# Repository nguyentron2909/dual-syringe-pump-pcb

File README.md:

# Dual Syringe Pump Controller (ESP32 + TMC2209)

This repository contains the KiCad hardware design for a compact, battery-powered dual stepper motor controller. Designed around the **ESP32-WROOM-32** for wireless control and **TMC2209** silent stepper drivers, this board is optimized for high-precision multi-channel micropump systems and drug delivery applications.

## 🛠 Hardware Architecture

The project is divided into three main functional blocks:

### 1. Power Management & Charging
A robust power subsystem designed to handle both wall power and battery operation, ensuring uninterrupted dispensing.
* **Charging:** Integrated **TP5100** battery charger for 2S Li-ion setups.
* **Regulation:** * **Buck Converter (LM2596):** Stepping down input voltage to 5V for logic.
    * **LDO (AMS1117-3.3):** Providing stable 3.3V for the ESP32 and sensors.
    * **Dual Boost Converters (XL6009):** Independent 12V rails (`+12V_1` and `+12V_2`) to power the stepper drivers, allowing for high-torque performance even on battery power.

### 2. Main Control & Interface
The logic center of the board, featuring:
* **MCU:** ESP32-WROOM-32 with USB-C programming via **CH340C** and an auto-reset circuit.
* **Position Feedback:** Support for dual **AS5600** magnetic encoders via I2C for closed-loop monitoring and exact position tracking.
* **User Interface:** Headers for an external screen, status LEDs, and additional tactile buttons.

### 3. Stepper Driver Stage
High-performance motor control featuring:
* **Drivers:** Dual **TMC2209-LA** drivers (U6 & U7).
* **Communication:** UART interface mapped to the ESP32 for advanced configuration (StealthChop, StallGuard, dynamic current limits).
* **Optimization:** Support for hardware-level current sensing. *(Note: RS resistors should be desoldered from the current sensing module for better performance, as noted in the schematic).*

---

## 📋 Key Specifications

| Component | Specification |
| :--- | :--- |
| **Microcontroller** | ESP32-WROOM-32 (Wi-Fi/BT) |
| **Stepper Drivers** | 2x TMC2209 (SilentStepStick style) |
| **Input Voltage** | +12V Adapter or 2S Li-ion Battery |
| **Logic Voltage** | 3.3V and 5V |
| **Sensors** | 2x AS5600 Magnetic Encoders |
| **USB Interface** | USB-C (CH340C) |

---

## 📂 PCB layout

---

## 📝 Design Notes

* **Current Sensing:** Ensure you desolder the RS resistors from the driver modules if you are using an external current sensing setup to avoid interference.
* **Thermal Management:** Provide adequate cooling (heatsinks/airflow) for the XL6009 boost converters and TMC2209 drivers if running the stepper motors at high continuous currents.
* **Big thanks to google gemini for writting this for me :D

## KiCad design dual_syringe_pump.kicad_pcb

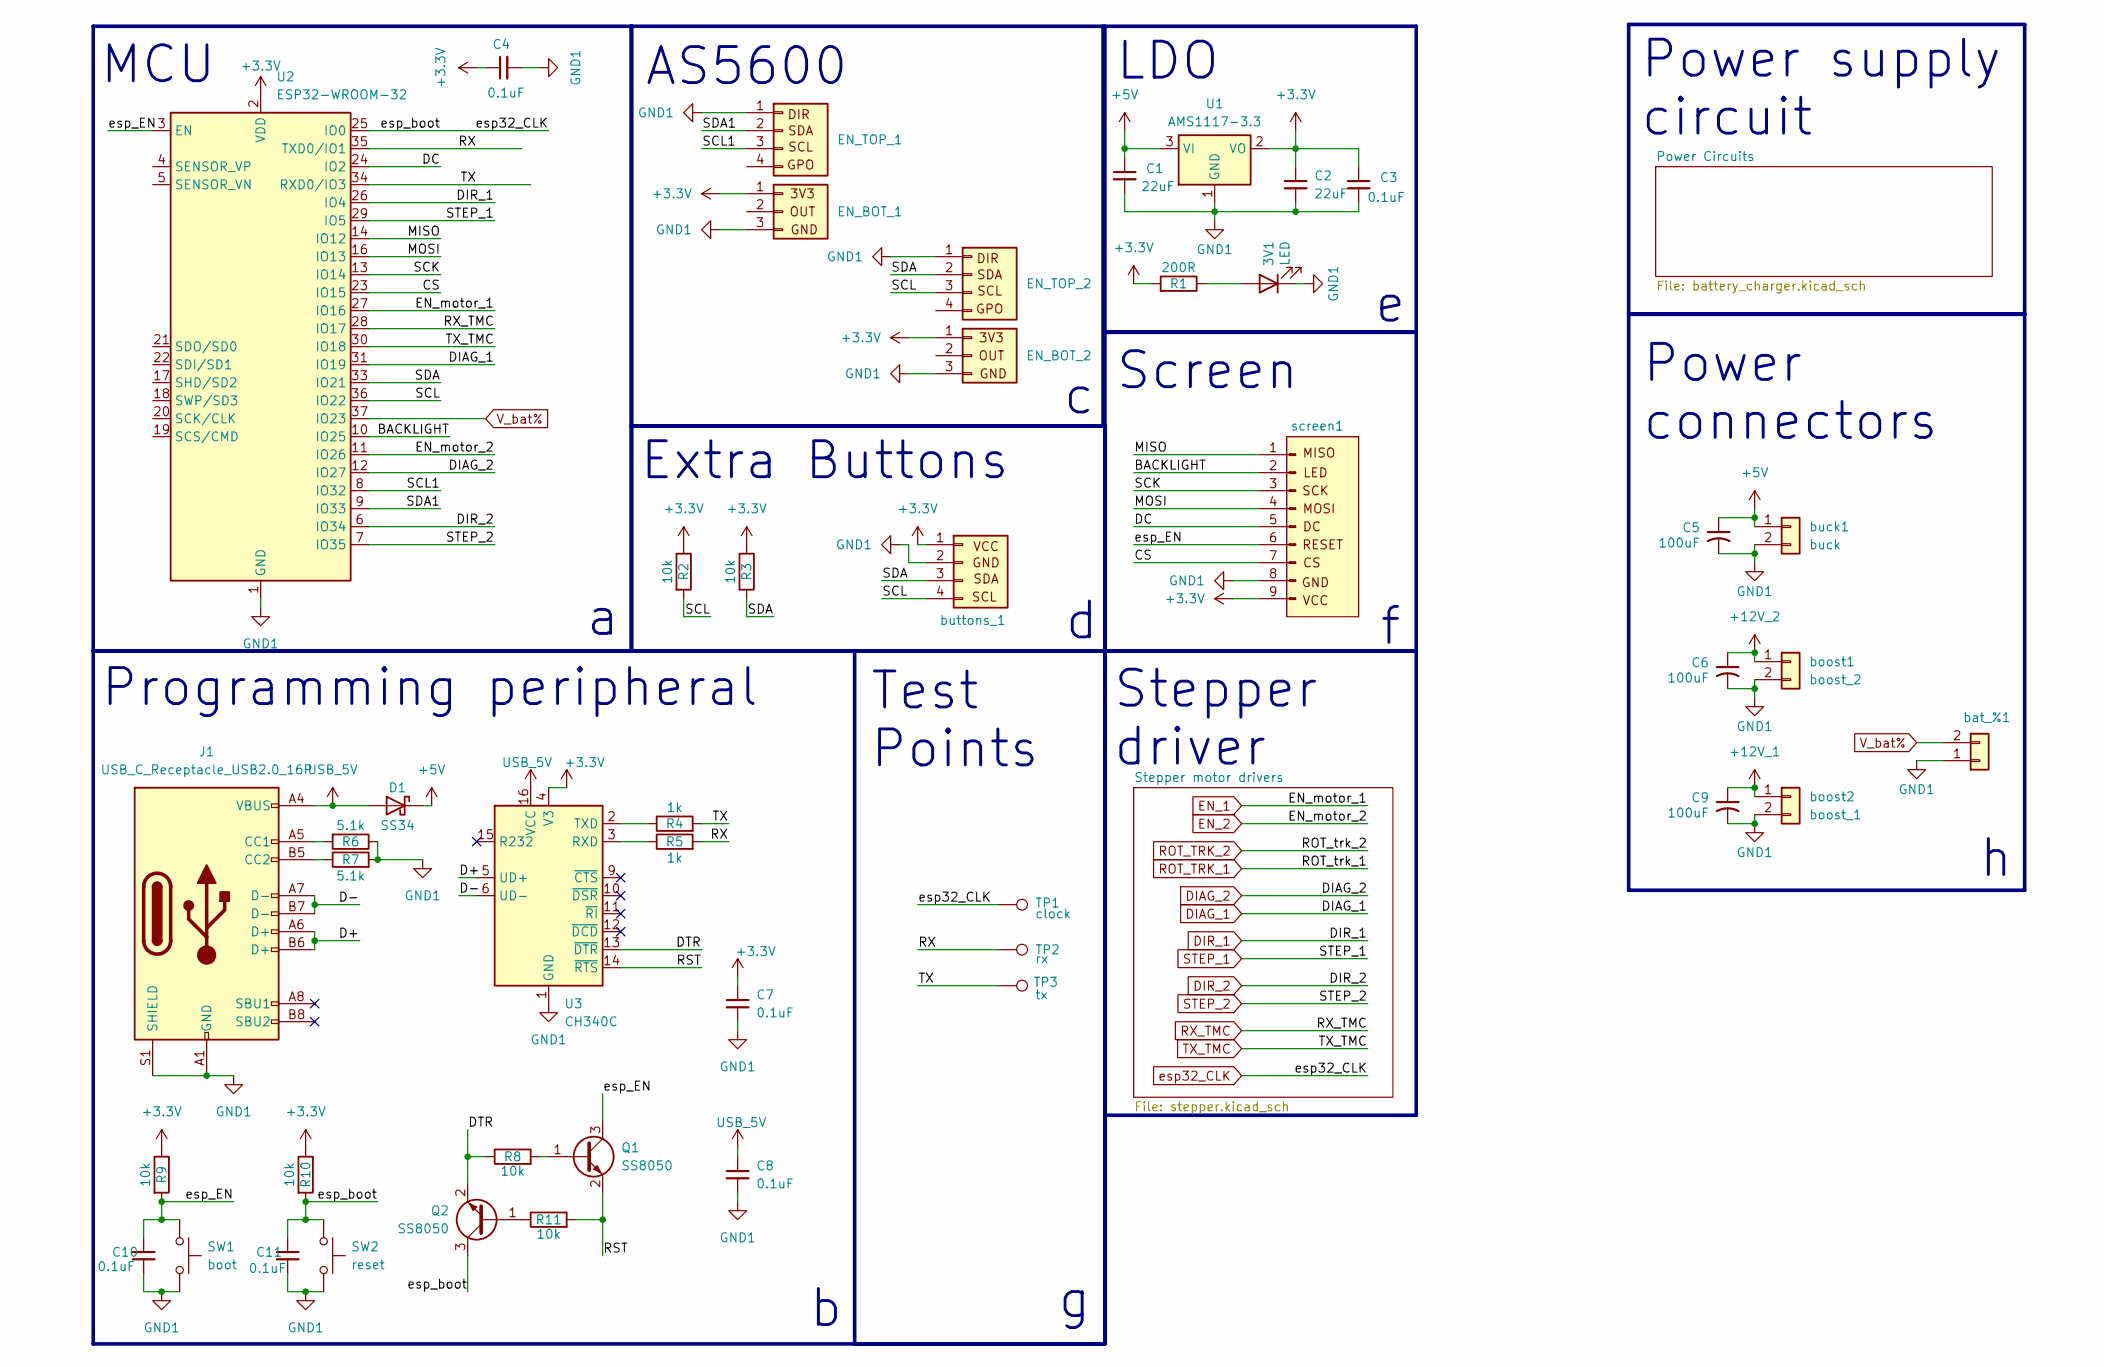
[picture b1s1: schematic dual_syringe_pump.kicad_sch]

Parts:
3V1: LED; LED_0603_1608Metric_Pad1.05x0.95mm
C1, C2: 22uF; C_0603
C3, C4, C7, C8, C10, C11: 0.1uF; C_0603
C5, C6, C9: 100uF; C_Elec_6.3x7.7
D1: SS34; D_SMA
EN_BOT_1, EN_BOT_2: Conn_01x03; PinHeader_1x03_P2.54mm_Vertical
EN_TOP_1, EN_TOP_2: Conn_01x04; PinHeader_1x04_P2.54mm_Vertical; Part Number 1-0401FBV0T
J1: USB_C_Receptacle_USB2.0_16P; USB_C_Receptacle_GCT_USB4105-xx-A_16P_TopMnt_Horizontal
Q1, Q2: SS8050; SOT-23
R1: 200R; R_0603
R2, R3, R8, R9, R10, R11: 10k; R_0603
R4, R5: 1k; R_0603
R6, R7: 5.1k; R_0603
SW1: boot; SW_SPST_CK_RS282G05A3
SW2: reset; SW_SPST_CK_RS282G05A3
TP1: clock; TestPoint_Pad_D1.0mm
TP2: rx; TestPoint_Pad_D1.0mm
TP3: tx; TestPoint_Pad_D1.0mm
U1: AMS1117-3.3; SOT-223-3_TabPin2
U2: ESP32-WROOM-32
U3: CH340C; SOIC-16_3.9x9.9mm_P1.27mm
bat_%1: battery _percentage; PinHeader_1x02_P2.54mm_Vertical; Part Number 1-0201FBV0T
boost1: boost_2; JST_VH_B2P-VH-B_1x02_P3.96mm_Vertical; Part Number 1-0201FBV0T
boost2: boost_1; JST_VH_B2P-VH-B_1x02_P3.96mm_Vertical; Part Number 1-0201FBV0T
buck1: buck; JST_VH_B2P-VH-B_1x02_P3.96mm_Vertical; Part Number 1-0201FBV0T
buttons_1: Conn_01x04; PinHeader_1x04_P2.54mm_Vertical; Part Number 1-0401FBV0T
screen1: Conn_01x09_Pin; PinSocket_1x09_P2.54mm_Vertical

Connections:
+3.3V: C2.1, C3.1, C4.1, C7.1, EN_BOT_1.1, EN_BOT_2.1, R1.2, R2.1, R3.1, R9.1, R10.1, U1.2 (VO), U2.2 (VDD), U3.4 (V3), buttons_1.1, screen1.9; also elsewhere on the board
+5V: C1.1, C5.1, D1.1 (K), U1.3 (VI), buck1.1; also elsewhere on the board
+12V_1: C9.1, boost2.1; also elsewhere on the board
+12V_2: C6.1, boost1.1; also elsewhere on the board
/BACKLIGHT: U2.10 (IO25), screen1.2
/CS: U2.23 (IO15), screen1.7
/D+: J1.A6 (D+), J1.B6 (D+), U3.5 (UD+)
/D-: J1.A7 (D-), J1.B7 (D-), U3.6 (UD-)
/DC: U2.24 (IO2), screen1.5
/DTR: Q2.2 (E), R8.1, U3.13 (~DTR)
/MISO: U2.14 (IO12), screen1.1
/MOSI: U2.16 (IO13), screen1.4
/RST: Q1.2 (E), R11.2, U3.14 (~RTS)
/RX: R5.2, TP2.1 (1_1), U2.35 (TXD0/IO1)
/SCK: U2.13 (IO14), screen1.3
/SCL: EN_TOP_2.3, R2.2, U2.36 (IO22), buttons_1.4
/SCL1: EN_TOP_1.3, U2.8 (IO32)
/SDA: EN_TOP_2.2, R3.2, U2.33 (IO21), buttons_1.3
/SDA1: EN_TOP_1.2, U2.9 (IO33)
/TX: R4.2, TP3.1 (1_1), U2.34 (RXD0/IO3)
/esp_EN: C10.1, Q1.3 (C), R9.2, SW1.1, U2.3 (EN), screen1.6
DIAG_1: U2.31 (IO19); also elsewhere on the board
DIAG_2: U2.12 (IO27); also elsewhere on the board
DIR_1: U2.26 (IO4); also elsewhere on the board
DIR_2: U2.6 (IO34); also elsewhere on the board
EN_1: U2.27 (IO16); also elsewhere on the board
EN_2: U2.11 (IO26); also elsewhere on the board
GND1: 3V1.1 (K), C1.2, C2.2, C3.2, C4.2, C5.2, C6.2, C7.2, C8.2, C9.2, C10.2, C11.2, EN_BOT_1.3, EN_BOT_2.3, EN_TOP_1.1, EN_TOP_2.1, J1.A1 (GND), J1.A12 (GND), J1.B1 (GND), J1.B12 (GND), J1.S1 (SHIELD), R6.1, R7.2, SW1.2, SW2.2, U1.1 (GND), U2.1 (GND), U2.15 (GND), U2.38 (GND), U2.39 (GND), U3.1 (GND), bat_%1.1, boost1.2, boost2.2, buck1.2, buttons_1.2, screen1.8; also elsewhere on the board
unnamed: 3V1.2 (A), R1.1
unnamed: J1.A5 (CC1), R6.2
unnamed: J1.B5 (CC2), R7.1
unnamed: Q1.1 (B), R8.2
unnamed: Q2.1 (B), R11.1
unnamed: R5.1, U3.3 (RXD)
unnamed: R4.1, U3.2 (TXD)
RX_TMC: U2.28 (IO17); also elsewhere on the board
STEP_1: U2.29 (IO5); also elsewhere on the board
STEP_2: U2.7 (IO35); also elsewhere on the board
TX_TMC: U2.30 (IO18); also elsewhere on the board
USB_5V: C8.1, D1.2 (A), J1.A4 (VBUS), J1.A9 (VBUS), J1.B4 (VBUS), J1.B9 (VBUS), U3.16 (VCC)
V_bat%: U2.37 (IO23), bat_%1.2; also elsewhere on the board
esp32_CLK: C11.1, Q2.3 (C), R10.2, SW2.1, TP1.1 (1_1), U2.25 (IO0); also elsewhere on the board

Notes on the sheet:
Test Points
Power supply circuit
Screen
Programming peripheral
Extra Buttons
LDO
MCU
Stepper driver
AS5600
Power connectors

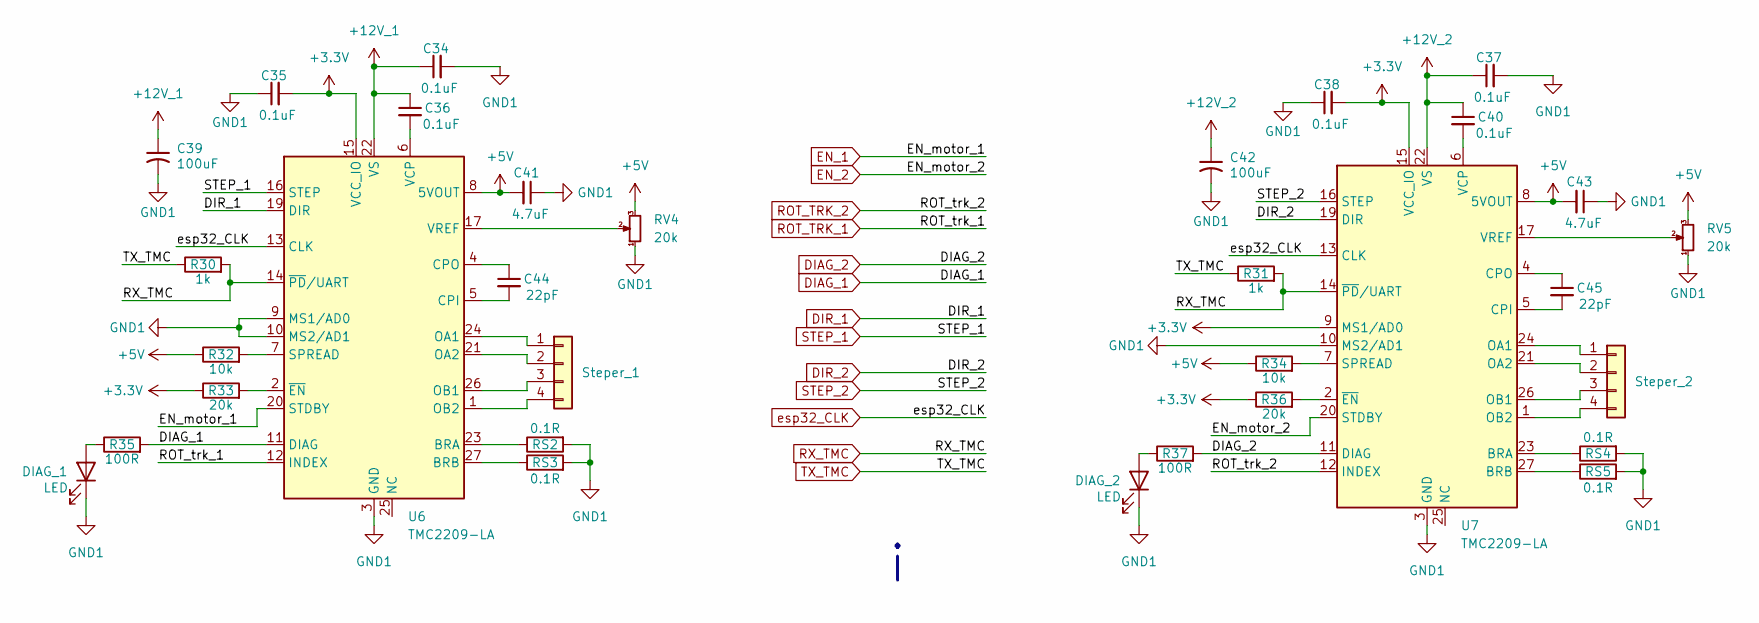
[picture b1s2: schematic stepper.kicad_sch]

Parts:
C34, C35, C36, C37, C38, C40: 0.1uF; C_0603
C39, C42: 100uF; CP_EIA-3216-12_Kemet-S_HandSolder
C41, C43: 4.7uF; C_0603
C44, C45: 22pF; C_0603
DIAG_1, DIAG_2: LED; LED_0603_1608Metric_Pad1.05x0.95mm
R30, R31: 1k; R_0603
R32, R34: 10k; R_0603
R33, R36: 20k; R_0603
R35, R37: 100R; R_0603
RS2, RS3, RS4, RS5: 0.1R; R_1206_3216Metric
RV4, RV5: 20k; Potentiometer_Bourns_TC33X_Vertical
Steper_1, Steper_2: Conn_01x04; PinHeader_1x04_P2.54mm_Vertical; Part Number 1-0401FBV0T
U6, U7: TMC2209-LA; VQFN-28-1EP_5x5mm_P0.5mm_EP3.7x3.7mm_ThermalVias

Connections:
+3.3V: C35.2, C38.2, R33.1, R36.1, U6.15 (VCC_IO), U7.9 (MS1/AD0), U7.15 (VCC_IO); also elsewhere on the board
+5V: C41.2, C43.2, R32.1, R34.1, RV4.3, RV5.3, U6.8 (5VOUT), U7.8 (5VOUT); also elsewhere on the board
+12V_1: C34.1, C36.1, C39.1, U6.22 (VS), U6.28 (VS); also elsewhere on the board
+12V_2: C37.1, C40.1, C42.1, U7.22 (VS), U7.28 (VS); also elsewhere on the board
DIAG_1: R35.2, U6.11 (DIAG); also elsewhere on the board
DIAG_2: R37.2, U7.11 (DIAG); also elsewhere on the board
DIR_1: U6.19 (DIR); also elsewhere on the board
DIR_2: U7.19 (DIR); also elsewhere on the board
EN_1: U6.20 (STDBY); also elsewhere on the board
EN_2: U7.20 (STDBY); also elsewhere on the board
GND1: C34.2, C35.1, C37.2, C38.1, C39.2, C41.1, C42.2, C43.1, DIAG_1.1 (K), DIAG_2.1 (K), RS2.2, RS3.2, RS4.2, RS5.2, RV4.1, RV5.1, U6.3 (GND), U6.9 (MS1/AD0), U6.10 (MS2/AD1), U6.18 (GND), U6.29 (GND), U7.3 (GND), U7.10 (MS2/AD1), U7.18 (GND), U7.29 (GND); also elsewhere on the board
unnamed: DIAG_1.2 (A), R35.1
unnamed: DIAG_2.2 (A), R37.1
unnamed: Steper_1.1, U6.24 (OA1)
unnamed: Steper_1.2, U6.21 (OA2)
unnamed: Steper_1.3, U6.26 (OB1)
unnamed: Steper_1.4, U6.1 (OB2)
unnamed: Steper_2.1, U7.24 (OA1)
unnamed: Steper_2.2, U7.21 (OA2)
unnamed: Steper_2.3, U7.26 (OB1)
unnamed: Steper_2.4, U7.1 (OB2)
unnamed: RS2.1, U6.23 (BRA)
unnamed: RS3.1, U6.27 (BRB)
unnamed: C44.2, U6.5 (CPI)
unnamed: C44.1, U6.4 (CPO)
unnamed: R32.2, U6.7 (SPREAD)
unnamed: C36.2, U6.6 (VCP)
unnamed: RV4.2, U6.17 (VREF)
unnamed: R33.2, U6.2 (~EN)
unnamed: RS4.1, U7.23 (BRA)
unnamed: RS5.1, U7.27 (BRB)
unnamed: C45.2, U7.5 (CPI)
unnamed: C45.1, U7.4 (CPO)
unnamed: R34.2, U7.7 (SPREAD)
unnamed: C40.2, U7.6 (VCP)
unnamed: RV5.2, U7.17 (VREF)
unnamed: R36.2, U7.2 (~EN)
ROT_TRK_1: U6.12 (INDEX)
ROT_TRK_2: U7.12 (INDEX)
RX_TMC: R30.2, R31.2, U6.14 (~PD/UART), U7.14 (~PD/UART); also elsewhere on the board
STEP_1: U6.16 (STEP); also elsewhere on the board
STEP_2: U7.16 (STEP); also elsewhere on the board
TX_TMC: R30.1, R31.1; also elsewhere on the board
esp32_CLK: U6.13 (CLK), U7.13 (CLK); also elsewhere on the board

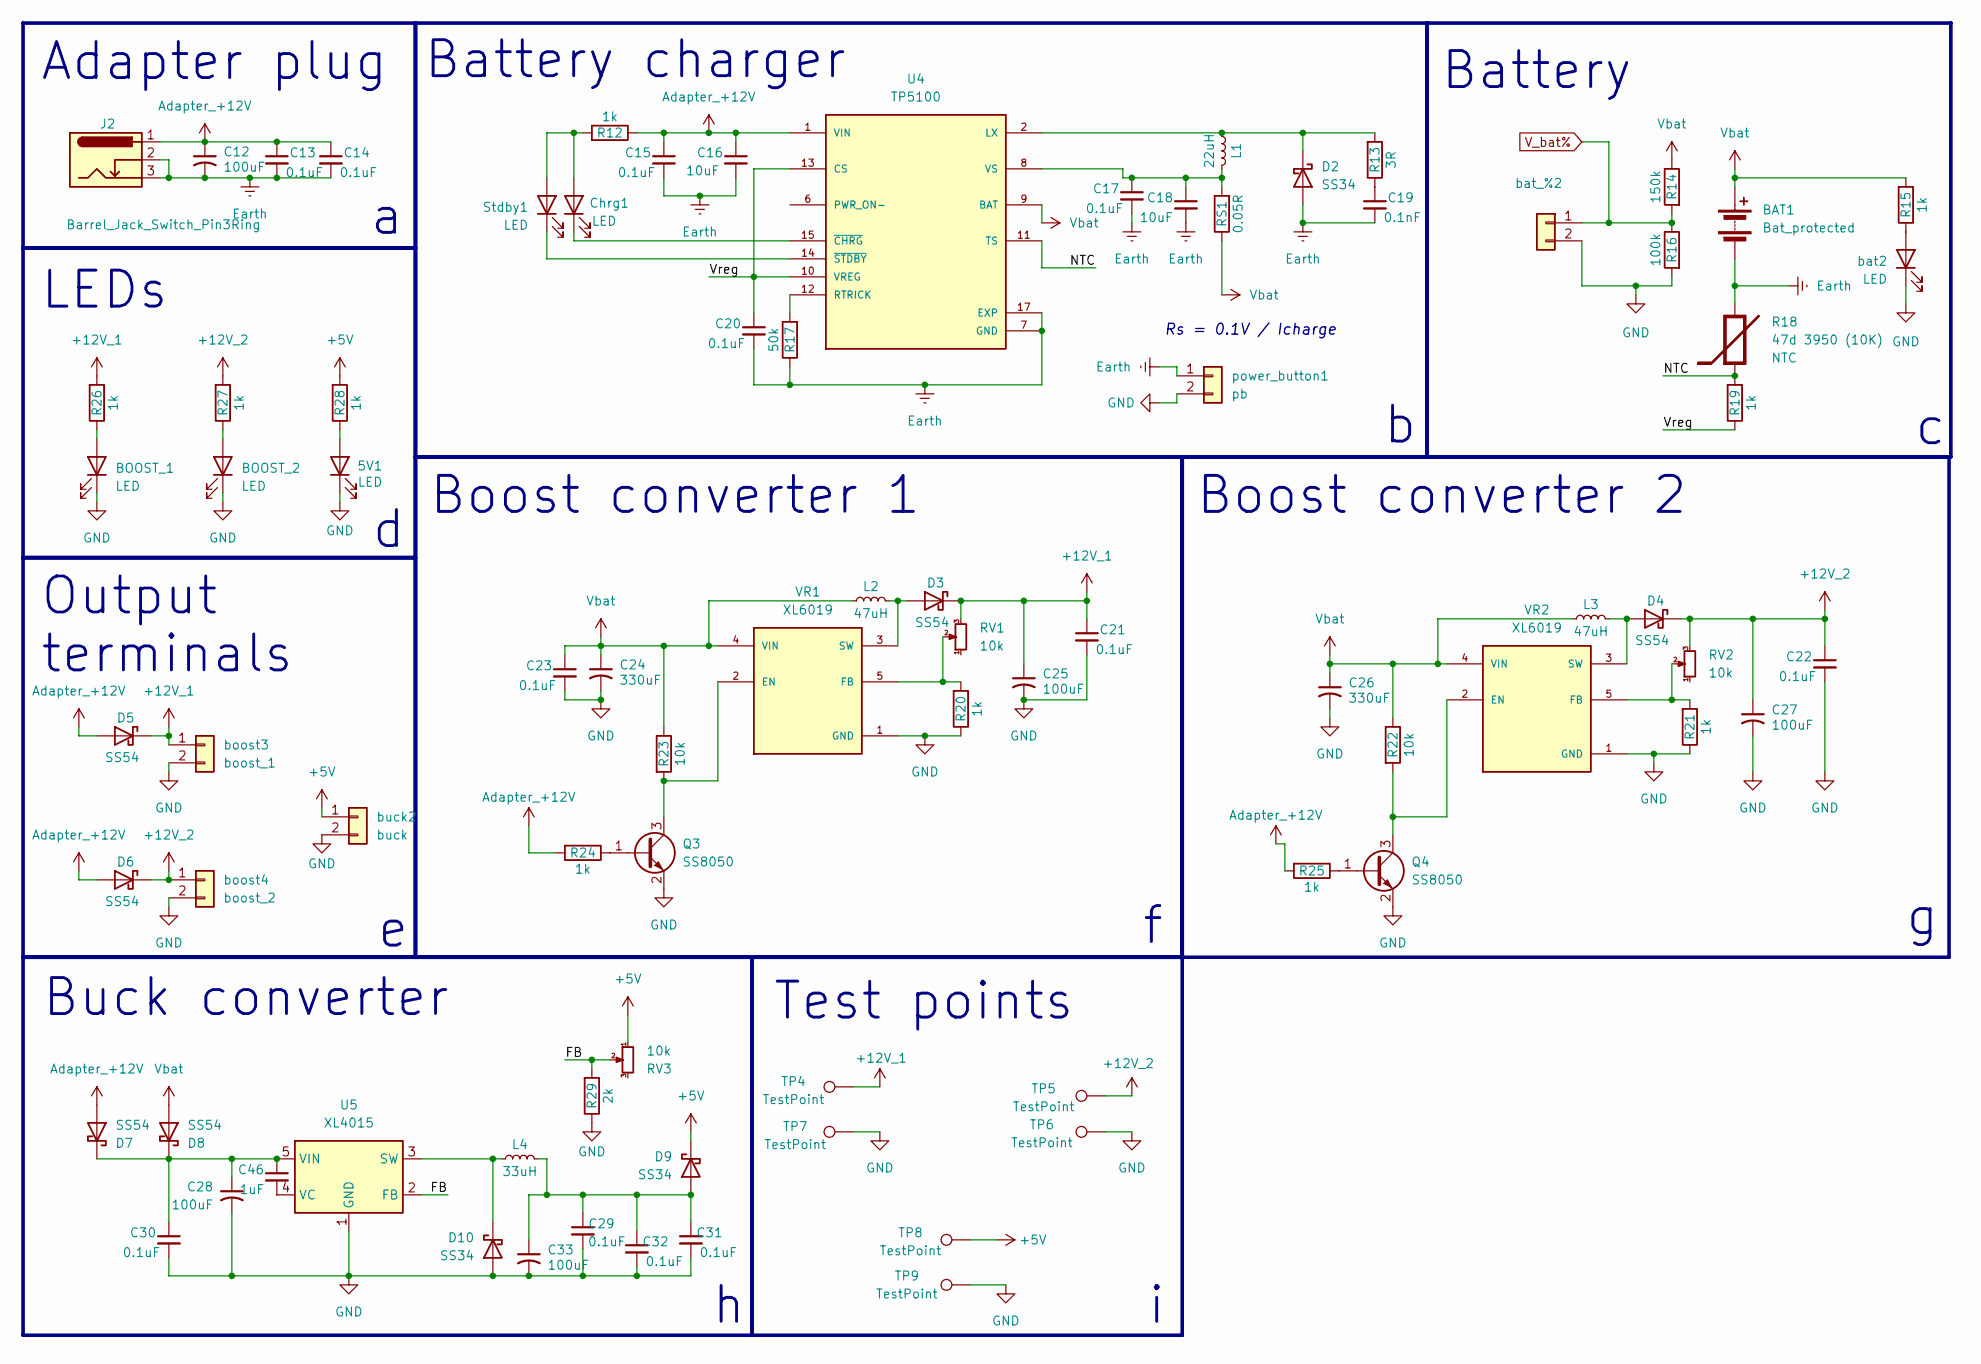
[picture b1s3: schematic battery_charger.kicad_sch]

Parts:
5V1: LED; LED_0603_1608Metric_Pad1.05x0.95mm
BAT1: Bat_protected; JST_VH_B2P-VH-B_1x02_P3.96mm_Vertical
BOOST_1, BOOST_2: LED; LED_0603_1608Metric_Pad1.05x0.95mm
C12, C28, C33: 100uF; C_Elec_6.3x7.7
C13, C14, C15, C17, C20, C21, C22, C23, C29, C30, C31, C32: 0.1uF; C_0603
C16, C18: 10uF; C_0603
C19: 0.1nF; C_0603
C24, C26: 330uF; C_Elec_6.3x7.7
C25, C27: 100uF; C_Elec_8x10.2
C46: 1uF; C_0603
Chrg1: LED; LED_0603_1608Metric_Pad1.05x0.95mm
D2, D9, D10: SS34; D_SMA
D3, D4: SS54; D_SMC
D5, D6, D7, D8: SS54; D_SMA
J2: Barrel_Jack_Switch_Pin3Ring; BarrelJack_GCT_DCJ200-10-A_Horizontal
L1: 22uH; L_7.3x7.3_H3.5
L2, L3: 47uH; L_SXN_SMDRI124
L4: 33uH; L_SXN_SMDRI124
Q3, Q4: SS8050; SOT-23
R12, R15, R19, R20, R21, R24, R25, R26, R27, R28: 1k; R_0603
R13: 3R; R_0603
R14: 150k; R_0603
R16: 100k; R_0603
R17: 50k; R_0603
R18: 47d 3950 (10K); PinHeader_1x02_P2.00mm_Vertical; Rating NTC
R22, R23: 10k; R_0603
R29: 2k; R_0603
RS1: 0.05R; R_1206_3216Metric
RV1, RV2, RV3: 10k; Potentiometer_Bourns_TC33X_Vertical
Stdby1: LED; LED_0603_1608Metric_Pad1.05x0.95mm
TP4, TP5, TP6, TP7, TP8, TP9: TestPoint; TestPoint_Pad_D1.0mm
U4: TP5100; QFN-16-1EP_4x4mm_P0.65mm_EP2.15x2.15mm_ThermalVias; PARTREV 2.3
U5: XL4015; TO-263-5_TabPin3
VR1, VR2: XL6019; TO-263-5_TabPin6_ThermalVias; PARTREV 1.1
bat2: LED; LED_0603_1608Metric_Pad1.05x0.95mm
bat_%2: battery _percentage; PinHeader_1x02_P2.54mm_Vertical; Part Number 1-0201FBV0T
boost3: boost_1; JST_VH_B2P-VH-B_1x02_P3.96mm_Vertical; Part Number 1-0201FBV0T
boost4: boost_2; JST_VH_B2P-VH-B_1x02_P3.96mm_Vertical; Part Number 1-0201FBV0T
buck2: buck; JST_VH_B2P-VH-B_1x02_P3.96mm_Vertical; Part Number 1-0201FBV0T
power_button1: pb; JST_VH_B2P-VH-B_1x02_P3.96mm_Vertical; Part Number 1-0201FBV0T

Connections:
+5V: D9.1 (K), R28.2, RV3.1, TP8.1 (1_1), buck2.1; also elsewhere on the board
+12V_1: C21.1, C25.1, D3.1 (K), D5.1 (K), R26.2, RV1.3, TP4.1 (1_1), boost3.1; also elsewhere on the board
+12V_2: C22.1, C27.1, D4.1 (K), D6.1 (K), R27.2, RV2.3, TP5.1 (1_1), boost4.1; also elsewhere on the board
/Power Circuits/FB: R29.2, RV3.2, U5.2 (FB)
/Power Circuits/NTC: R18.2 (-), R19.2, U4.11 (TS); also elsewhere on the board
/Power Circuits/Vreg: C20.1, R19.1, U4.10 (VREG), U4.13 (CS)
Adapter_+12V: C12.1, C13.1, C14.1, C15.1, C16.1, D5.2 (A), D6.2 (A), D7.2 (A), J2.1, R12.1, R24.2, R25.2, U4.1 (VIN), U4.4 (VIN), U4.5 (VIN), U4.16 (VIN)
Earth: BAT1.2 (-), C12.2, C13.2, C14.2, C15.2, C16.2, C17.2, C18.2, C19.2, C20.2, D2.2 (A), J2.2, J2.3, R17.1, R18.1 (+), U4.7 (GND), U4.17 (EXP), power_button1.1; also elsewhere on the board
GND: 5V1.1 (K), BOOST_1.1 (K), BOOST_2.1 (K), C21.2, C22.2, C23.2, C24.2, C25.2, C26.2, C27.2, C28.2, C29.2, C30.2, C31.2, C32.2, C33.2, D10.2 (A), Q3.2 (E), Q4.2 (E), R16.2, R20.1, R21.1, R29.1, TP6.1 (1_1), TP7.1 (1_1), TP9.1 (1_1), U5.1 (GND), VR1.1 (GND), VR2.1 (GND), bat2.1 (K), bat_%2.2, boost3.2, boost4.2, buck2.2, power_button1.2; also elsewhere on the board
unnamed: 5V1.2 (A), R28.1
unnamed: BOOST_1.2 (A), R26.1
unnamed: BOOST_2.2 (A), R27.1
unnamed: C19.1, R13.1
unnamed: Chrg1.2 (A), R12.2, Stdby1.2 (A)
unnamed: Chrg1.1 (K), U4.15 (~CHRG)
unnamed: D2.1 (K), L1.1, R13.2, U4.2 (LX), U4.3 (LX)
unnamed: D3.2 (A), L2.2, VR1.3 (SW), VR1.6 (SW)
unnamed: D4.2 (A), L3.2, VR2.3 (SW), VR2.6 (SW)
unnamed: C28.1, C30.1, C46.1, D7.1 (K), D8.1 (K), U5.5 (VIN)
unnamed: C29.1, C31.1, C32.1, C33.1, D9.2 (A), L4.2
unnamed: D10.1 (K), L4.1, U5.3 (SW)
unnamed: Q3.1 (B), R24.1
unnamed: Q3.3 (C), R23.2, VR1.2 (EN)
unnamed: Q4.1 (B), R25.1
unnamed: Q4.3 (C), R22.2, VR2.2 (EN)
unnamed: Stdby1.1 (K), U4.14 (~STDBY)
unnamed: R17.2, U4.12 (RTRICK)
unnamed: C17.1, C18.1, L1.2, RS1.2, U4.8 (VS)
unnamed: C46.2, U5.4 (VC)
unnamed: R20.2, RV1.2, VR1.5 (FB)
unnamed: R21.2, RV2.2, VR2.5 (FB)
unnamed: R15.1, bat2.2 (A)
V_bat%: R14.2, R16.1, bat_%2.1; also elsewhere on the board
Vbat: BAT1.1 (+), C23.1, C24.1, C26.1, D8.2 (A), L2.1, L3.1, R14.1, R15.2, R22.1, R23.1, RS1.1, U4.9 (BAT), VR1.4 (VIN), VR2.4 (VIN); also elsewhere on the board

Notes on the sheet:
Buck converter
Battery
Battery charger
Boost converter 2
Output terminals
Test points
Adapter plug
Rs = 0.1V / Icharge
Boost converter 1
LEDs

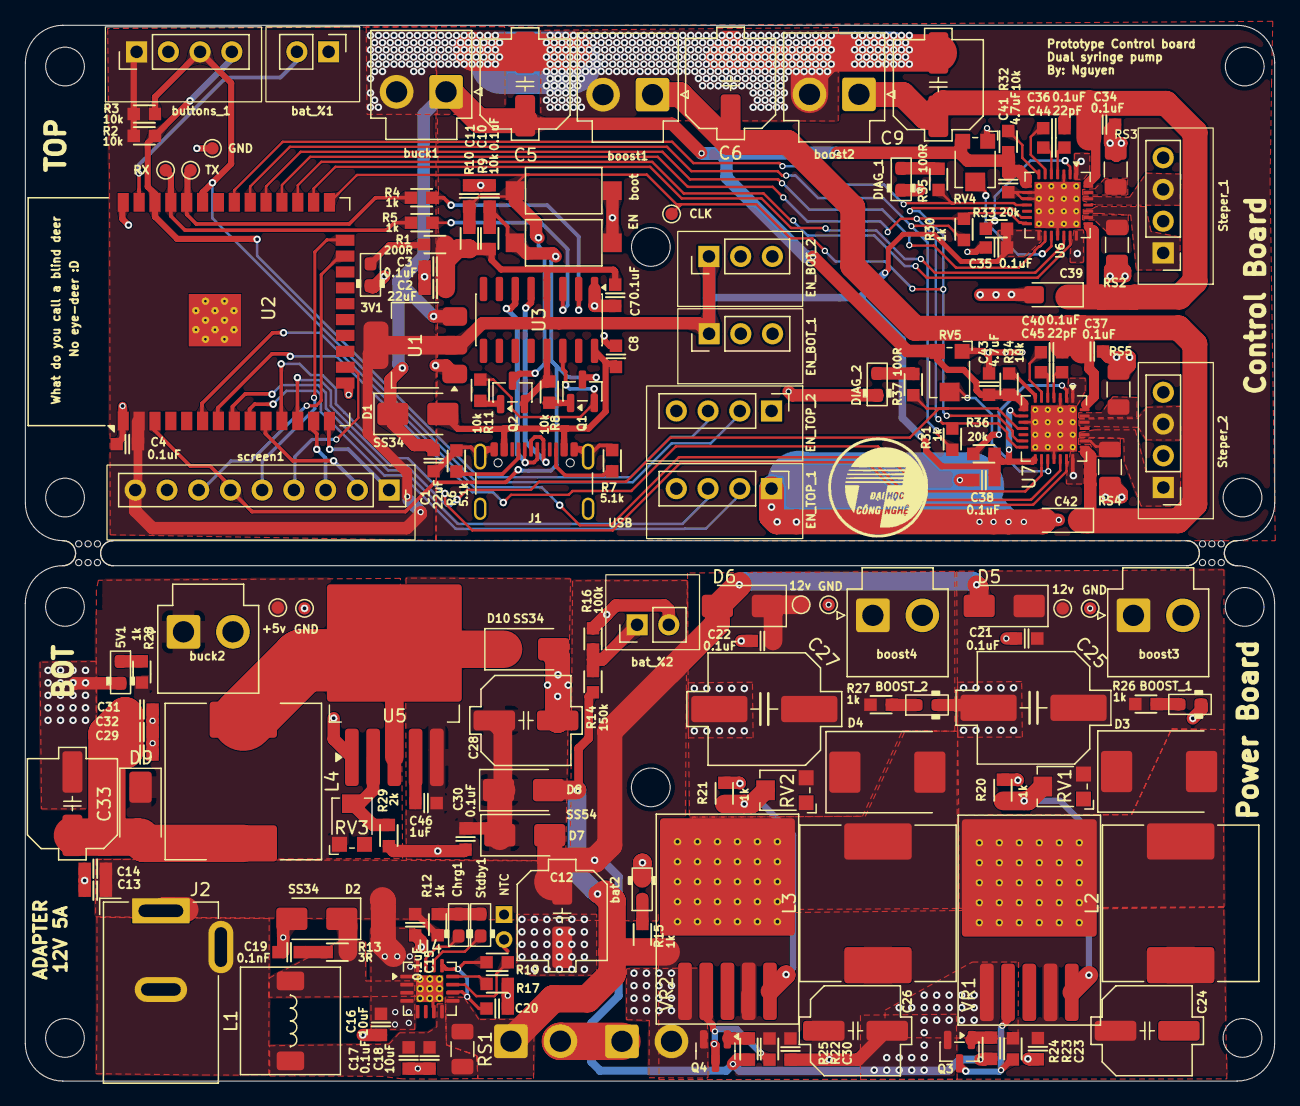
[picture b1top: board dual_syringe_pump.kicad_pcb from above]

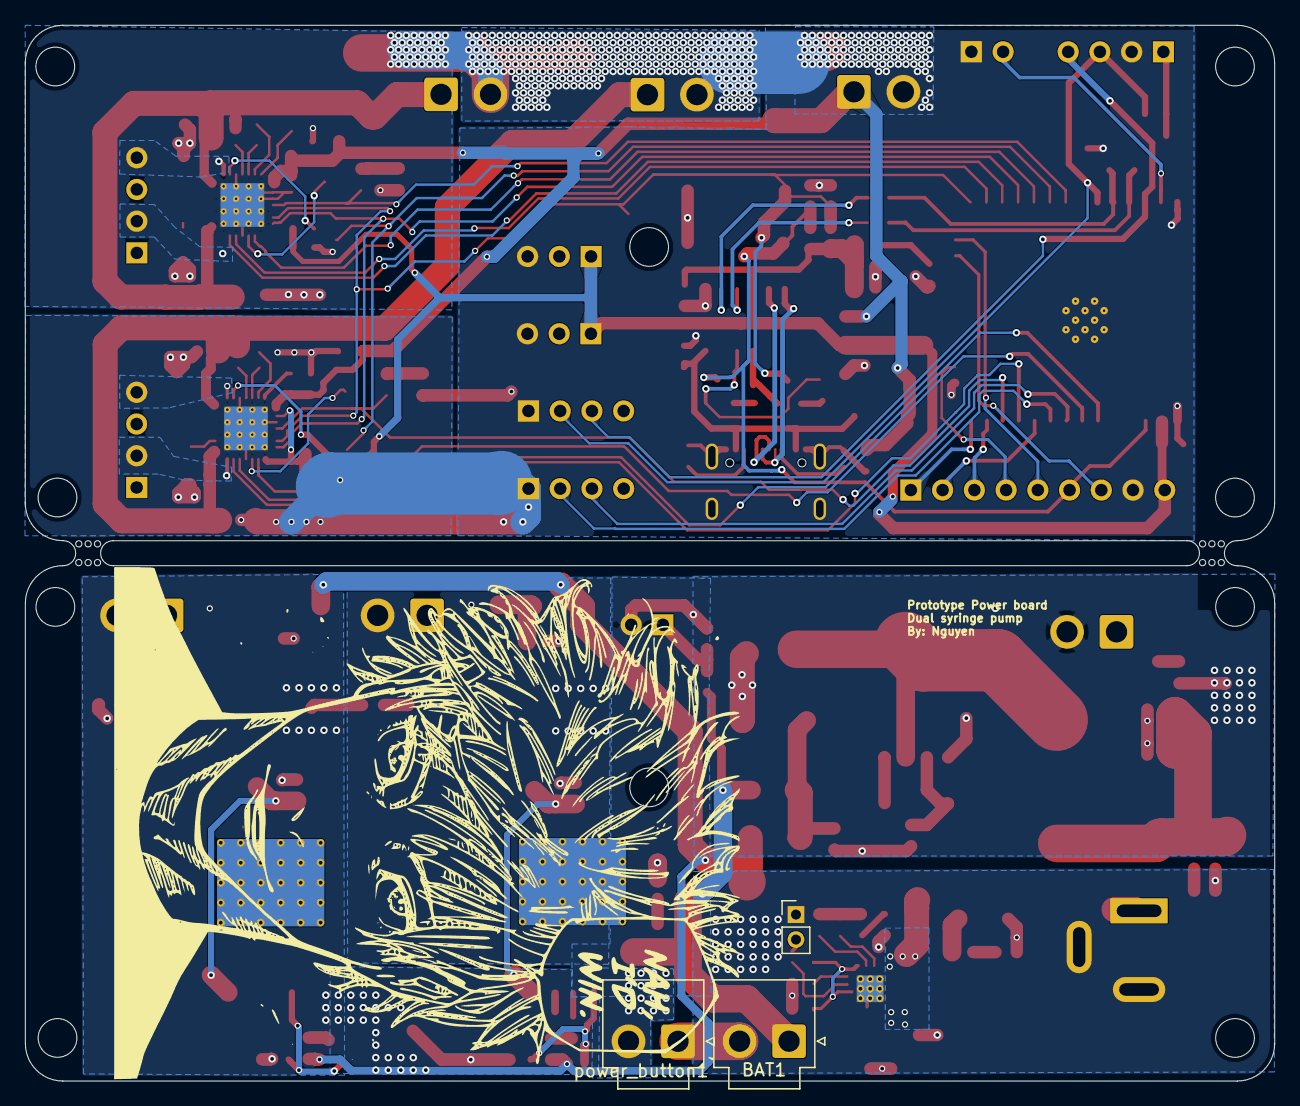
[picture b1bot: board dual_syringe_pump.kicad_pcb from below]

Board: 2 copper layers, 100.0 x 84.5 mm, 164 parts (3 on the bottom side), 98 nets.

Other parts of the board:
C30#2: 0.1u; C_0603
GND: TestPoint; TestPoint_Pad_D1.0mm
NTC: 47d 3950 (10K); PinHeader_1x02_P2.00mm_Vertical
mouse-bite-2mm-slot, mouse-bite-2mm-slot#2: VAL**; mouse-bite-2mm-slot

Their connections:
/Power Circuits/NTC: NTC.2 (-); also elsewhere on the board
Earth: NTC.1 (+); also elsewhere on the board
GND: C30#2.2; also elsewhere on the board
GND1: GND.1; also elsewhere on the board
Vbat: C30#2.1; also elsewhere on the board
